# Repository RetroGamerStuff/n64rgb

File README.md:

# N64 RGB 

A collection of RGB mods for the N64. This repository includes:

- a simple RGB amp
  * based on TI's video amplifier THS7374 / THS7373 (only for some NTSC-units)
  * folder: simpleRGBAmp
- a general RGB digital-to-analog converter based on viletims schematics
  * supported devices: MaxII (EPM240T100C5, EPM570T100C5) and MaxV (5M240ZT100C4, 5M570ZT100C4) CPLDs
  * PCB files (common for all supported devices) and firmware (separate programming files) are provided
  * folder: generalRGBmod
- an advanced RGB digital-to-analog converter with optional YPbPr conversion
  * supported FPGA: Cyclone IV EP4CE10E22 and Cyclone 10 LP 10CL010YE144
  * PCB files (common for all supported devices) and firmware (separate programming files) are provided
  * additional Filter board for the outputted video signal if you need that
  * folder: advancedRGBmod
- additional RCP-NUS Adapter (flexible PCB):
  * buffering of video signals for N64RGB/N64Adv installs with wires
  * PCB files provided
  * folder: misc/RCP2Pads
- additional RCP-NUS to N64RGBv2.1/N64Adv install adapter (long flexible PCB):
  * buffering of video signals for N64RGBv2.1/N64Adv
  * can be directly connected to modding board
  * PCB files provided
  * folder: misc/RCP2N64RGB
- Filter AddOn for N64RGBv2 and N64 Advanced:
  * used to filter the video signal comming out of the ADV7125 or to adjust signal levels such that one can use SNES PAL RGB cables
  * PCB files provided
  * folder: misc/FilterAddOn
- Filter AddOn as flexible PCB for N64RGBv2.1 and N64 Advanced:
  * used to filter the video signal comming out of the ADV7125 or to adjust signal levels such that one can use SNES PAL RGB cables
  * PCB files provided
  * folder: misc/N64RGB2MoutFilter
- additional power supply PCB for viletime N64RGB DAC and N64RGBv1
  * PCB files provided
  * folder: misc/PowerReg

## Acknowledgement

Of course, many thanks to viletim for his initial CPLD-based DAC project, for providing a valuable commercial modding board as well as for publishing the schematics and source codes for that project.
I also want to send many thanks to Ikari_01. He has written the code to detect 480i and PAL/NTSC output with the CPLD. He provides a source code for the XC9572XL, which can be accessed here: [URL to Ikari_01's GitHub repository](https://github.com/mrehkopf/n64rgb)
Last but not least, thank you to Bob for his website [RetroRGB](http://retrorgb.com) and especially in this context here for collecting and sharing all the [RGB information regarding the N64](http://retrorgb.com/n64.html).

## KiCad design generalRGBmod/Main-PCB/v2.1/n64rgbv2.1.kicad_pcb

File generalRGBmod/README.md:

# General N64 RGB Digital-to-Analog Mod

This folder contains all you need for a complete DIY RGB mod.

Please don't ask me for selling a modding. I either sell some prototypes on some forums marketplaces (which is very unlikely) or I don't have any of the boards.
This is a complete DIY modding project. So everybody is on his own here.
If you are looking for a ready to install kit, just look on your own for a seller. Preferably you should invest your money into a [kit made by viletim](http://etim.net.au/shop/shop.php?crn=209). I also provide similar firmware files for his board in another GitHub repository named [n64rgb_fw4viletim](https://github.com/borti4938/n64rgb_fw4viletim) (note that I do not provide support for the firmware port there).

**WARNING:** This is an advanced DIY project if you do everything on your own. You need decent soldering skills. The CPLD has 0.5mm fine pitch with 100pins. Next to it the video amp has a 0.65mm pin pitch on the board there are some SMD1206 resistor and ferrit bead arrays.

## Features

- Supporting for different CPLDs on a common PCB design:
  * MaxII EPM240T100C5
  * MaxII EPM570T100C5
  * MaxV 5M240ZT100C5
  * MaxV 5M570ZT100C5
- Video DAC:
  * V2: Video DAC ADV7125
- Detection of 240p/288p vs. 480i/576i together with detection of NTSC vs. PAL mode
- optional VI-De-Blur in 240p/288p (horizontal resolution decreased from 640 to 320 pixels)
- optional 16bit color mode
- IGR features:
  * reset the console with the controller (can be disabled via jumper)
  * full control on de-blur and 16bit mode with the controller (can be disabled via jumper)
- optional dedicated mechanical switches for toggling VI-Deblur and 16bit color mode

The following shortly describes the main features of the firmware and how to use / control them.

#### Notes

### In-Game Routines (IGR)

Three functionalities are implemented: toggle de-blur feature and toggle the 16bit mode as well as resetting the console.

The button combination are as follows:

- reset the console: Z + Start + R + A + B
- (de)activate de-blur:
  - deactivate: Z + Start + R + C-le
  - activate: Z + Start + R + C-ri
- (de)activate 16bit mode:
  - deactivate: Z + Start + R + C-up
  - activate: Z + Start + R + C-dw

_Modifiying the IGR Button Combinations_:  
It's difficult to make everybody happy with it. Third party controllers, which differ from the original ones by design, make it even more difficult. So it is possible to generate your own firmware with **your own** preferred **button combinations** implemented. Please refere to the document **IGR.README.md** located in the top folder of this repository for further information.

_Final remark on IGR_:  
However, as the communication between N64 and the controller goes over a single wire, sniffing the input is not an easy task (and probably my solution is not the best one). This together with the lack of an exhaustive testing (many many games out there as well my limited time), I'm looking forward to any incomming issue report to furhter improve this feature :)

### VI-DeBlur

VI-Deblur of the picture information is only be done in 240p/288p. This is be done by simply blanking every second pixel. Normally, the blanked pixels are used to introduce blur by the N64 in 240p/288p mode. However, some games like Mario Tennis, 007 Goldeneye, and some others use these pixel for additional information rather than for blurring effects. In other words this means that these games uses full horizontal resolution even in 240p/288p output mode. Hence, the picture looks more blurry in this case if de-blur feature is activated.

### 16bit Color Mode

The 16bit color mode reduces the color depth from 21bit (7bit for each color) downto 16bits (5bit for red and blue, 6bit for green). Some very few games processes the color information in 16bit. The 16bit color mode simply sets LSBs to '0'.

### Jumpers

There are five jumpers on the modding board - two double solder jumper and three standard jumper.  
For double jumper, jumper Jxx.1 is indicated by an arrow, Jxx.2 is on the opposite side.

- J11.1 -> activates VI-deblur if closed. **[1]**
- J11.2 -> activates 16bit color mode **[1]**
- J12.x -> disables IGR functions if closed
  - x.1: VI-DeBlur and 16bit mode toggle by controller
  - x.2: reset by controller
- J21 -> enables Sync on Green if closed
- J31 -> 75ohm CSync Level
  - open: ~1.87Vpp at a 75ohm termination, i.e. you need an additional resistor in your RGB cables sync line to further attenuate voltage level
  - closed: ~300mVpp at a 75ohm termination, which is standard, i.e. you must not have any components attached to your RGB cables sync line
- J2: toggles video low pass filter of the Filter AddOn
  - open: enabled
  - closed: bypassed 

**Notes**:  

**[1]**  
Jumper becomes active on power cycle or if toggled while running operation.  

## Technical Information

A complete installation and setup guide to this modding kit is provided in the main folder of the repository. Here are some additional short notes.

### Checklist: How to build the project

- Use PCB files to order your own PCB or simply use the shared project on OSHPark
- Source the components you need, e.g. from Mouser
- Wait for everything to arrive
- Assemble your PCB:
  * If you use a MaxII CPLD, you have to assemble FB3 and must not use U4, C41 and C42.
  * If you use a MaxV CPLD, you need U4 (a 1.8V voltage regulator), C41 and C42. Don't touch FB3 in this case!
- Flash the firmware to the CPLD:
  * You need a Altera USB Blaster
  * The board needs to be powered; so you may consider to install the PCB into your N64 first and then use the N64 for powering the board
  * If you want to build an adapter, you may take a look onto [my DIY adapter](https://oshpark.com/shared_projects/mEwjoesz) at [my profile on OSHPark](https://oshpark.com/profiles/borti4938)
- Install the modding board:
  * Installation description is part of the guide located in the top folder.
  * However an installation guide of a similar product made by viletim is provided [here](http://etim.net.au/n64rgb/). Keep in mind that there are minor differences.
  * You have to be aware of the pinout of your video-encoder build into your N64. Pads on the DIY modding board are labeled.

### Source the PCB
Choose the PCB service which suits you. Here are some:

- OSHPark: look onto [my profile](https://oshpark.com/profiles/borti4938)
- PCBWay.com: [Link](http://www.pcbway.com/), [Affiliate Link](http://www.pcbway.com/setinvite.aspx?inviteid=10658)

### BOM / Part List for the PCB
This part list a recommendation how the PCB is designed. If you are able to find pin-compatible devices / parts, you can use them.

The manufacturer's part numbers (MPNs) are just to help you to source appropriate components.

### Firmware
The firmware is located in the folder firmware/. To build the firmware on your own you need Quartus Prime Lite (any version which supports MaxII and MaxV devices).

If you only want to flash the firmware, the configuration files are pre-compiled and located in firmware/output_files. You need the POF appropriate for the CPLD you have choosen (look for the *\_extension*).

For flashing you need:

- Altera USB Blaster
- Standalone Quartus Prime Programmer and Tools

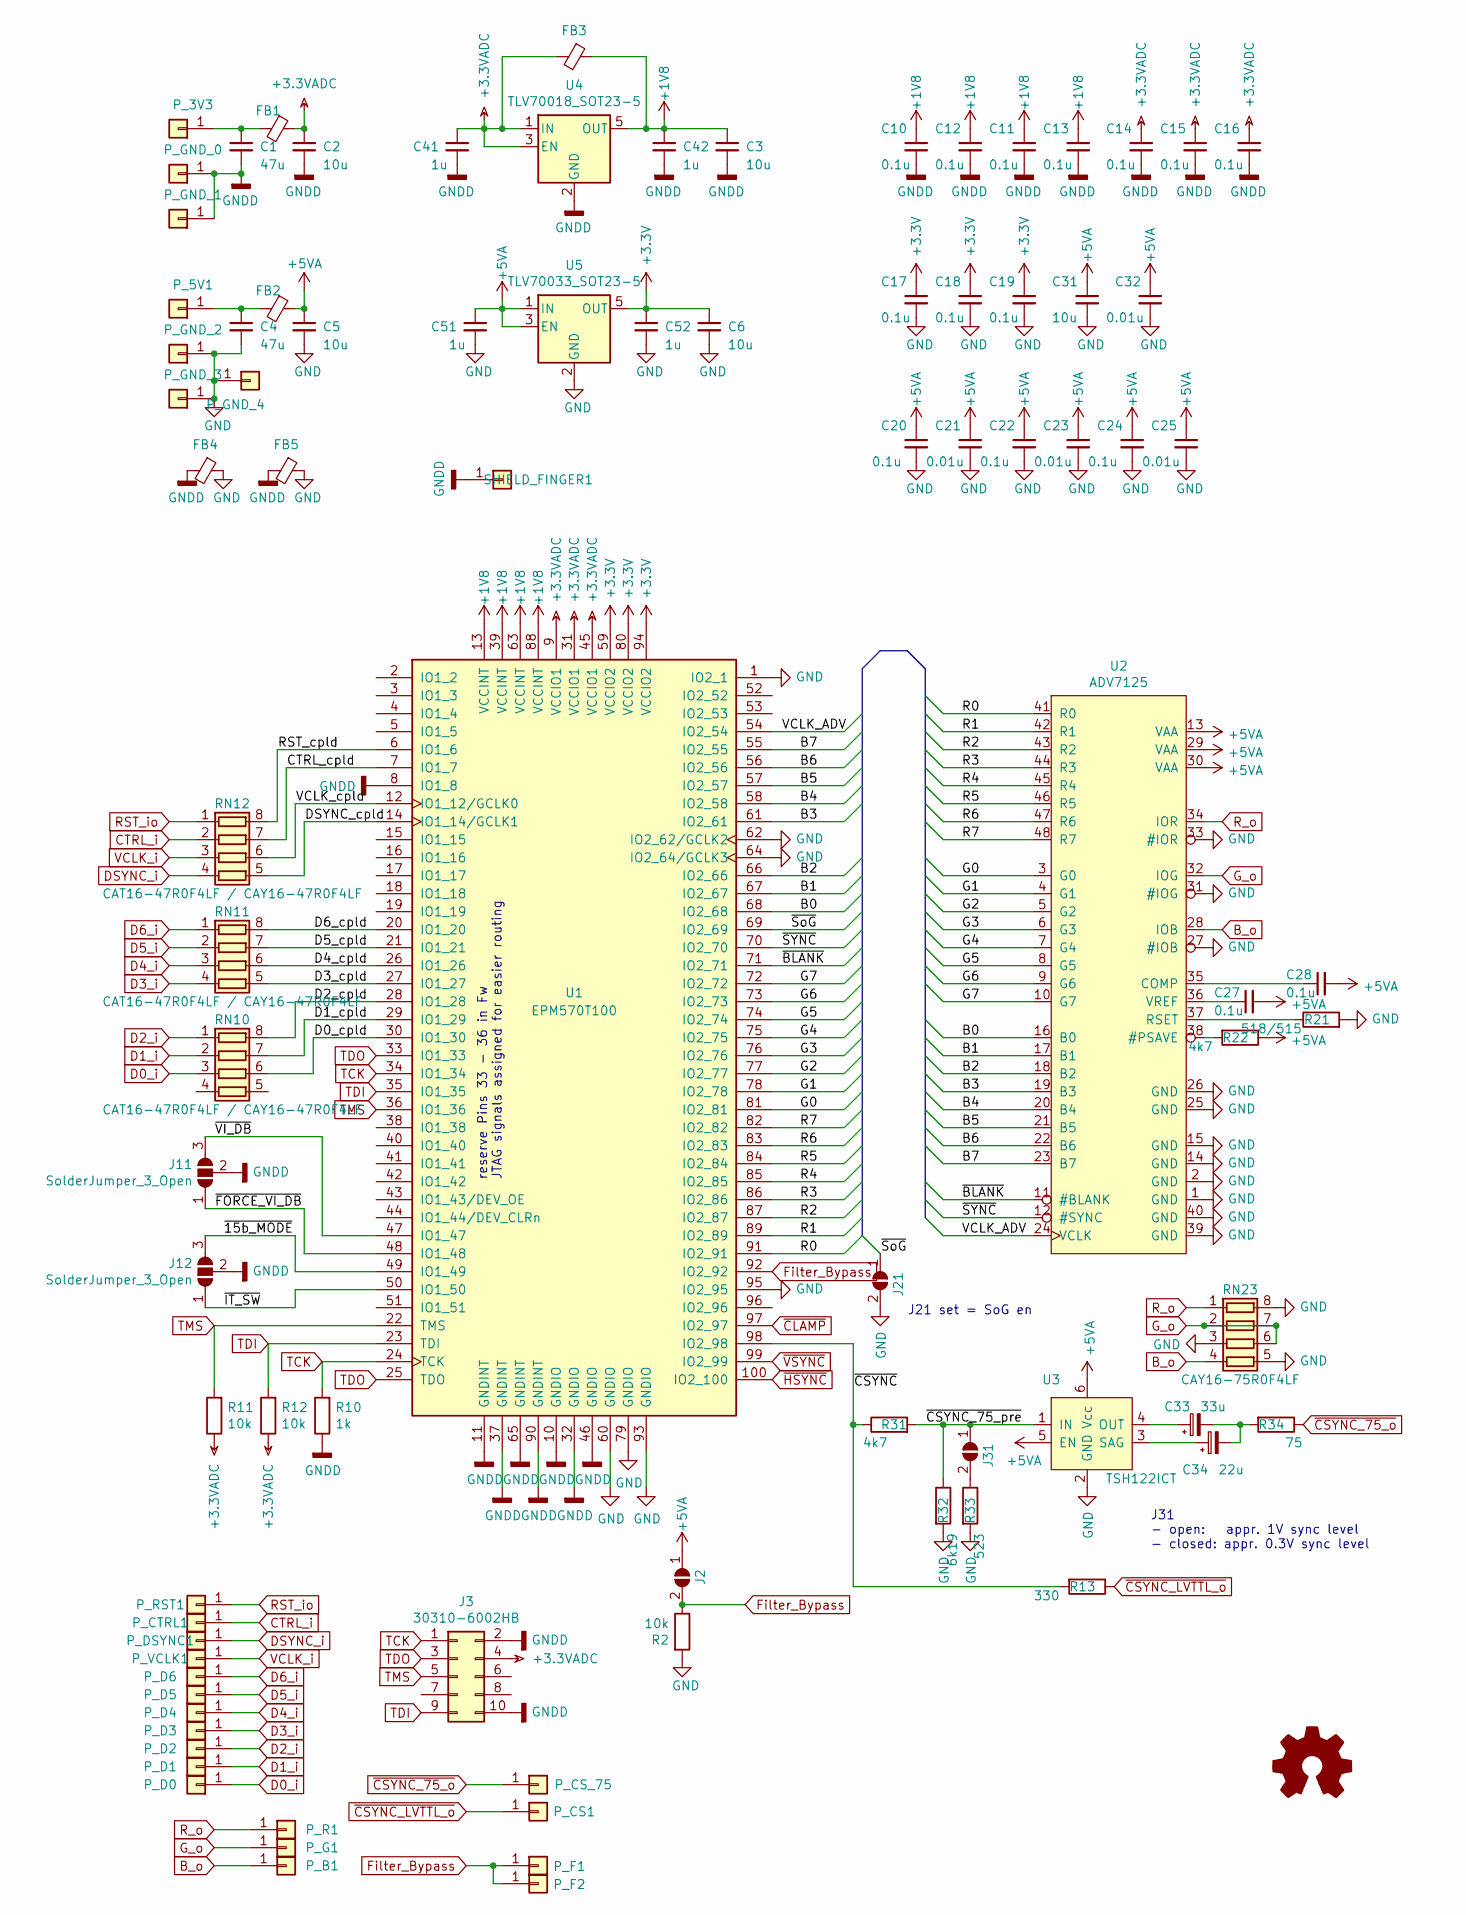
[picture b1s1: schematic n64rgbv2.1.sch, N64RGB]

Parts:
C1, C4: 47u; C_0805_2012Metric_Pad1.15x1.40mm_HandSolder
C2, C3, C5, C6, C31: 10u; C_0805_2012Metric_Pad1.15x1.40mm_HandSolder
C10, C11, C12, C13, C14, C15, C16, C17, C18, C19, C20, C22, C24, C27, C28: 0.1u; C_0603_1608Metric_Pad1.05x0.95mm_HandSolder
C21, C23, C25, C32: 0.01u; C_0603_1608Metric_Pad1.05x0.95mm_HandSolder
C33: 33u; C_0805_2012Metric_Pad1.15x1.40mm_HandSolder
C34: 22u; C_0805_2012Metric_Pad1.15x1.40mm_HandSolder
C41, C42, C51, C52: 1u; C_0603_1608Metric_Pad1.05x0.95mm_HandSolder
FB1, FB2, FB3, FB4, FB5: MPZ1608S221ATA00; R_0603_1608Metric_Pad1.05x0.95mm_HandSolder
J2, J21, J31: SolderJumper_2_Open; SolderJumper-2_P1.3mm_Open_RoundedPad1.0x1.5mm
J3: 30310-6002HB; PinHeader_2x05_P2.54mm_Vertical
J11, J12: SolderJumper_3_Open; SolderJumper-3_P1.3mm_Open_RoundedPad1.0x1.5mm
P_3V3, P_5V1: Conn_01x01; Wirepad_1.27_2.54
P_B1: Conn_01x01; Wirepad_1.27_2.54
P_CS1: Conn_01x01; Wirepad_1.27_2.54
P_CS_75: Conn_01x01; Wirepad_1.27_2.54
P_CTRL1: Conn_01x01; Wirepad_0.8_1.6
P_D0, P_D1, P_D2, P_D3, P_D4, P_D5, P_D6: Conn_01x01; Wirepad_0.8_1.6
P_DSYNC1: Conn_01x01; Wirepad_0.8_1.6
P_F1, P_F2: Conn_01x01; Wirepad_1.27_2.54
P_G1: Conn_01x01; Wirepad_1.27_2.54
P_GND_0, P_GND_1, P_GND_2, P_GND_3, P_GND_4: Conn_01x01; Wirepad_1.27_2.54
P_R1: Conn_01x01; Wirepad_1.27_2.54
P_RST1: Conn_01x01; Wirepad_0.8_1.6
P_VCLK1: Conn_01x01; Wirepad_0.8_1.6
R2, R11, R12: 10k; R_0603_1608Metric_Pad1.05x0.95mm_HandSolder
R10: 1k; R_0603_1608Metric_Pad1.05x0.95mm_HandSolder
R13: 330; R_0603_1608Metric_Pad1.05x0.95mm_HandSolder
R21: 518/515; R_0603_1608Metric_Pad1.05x0.95mm_HandSolder
R22, R31: 4k7; R_0603_1608Metric_Pad1.05x0.95mm_HandSolder
R32: 6k19; R_0603_1608Metric_Pad1.05x0.95mm_HandSolder
R33: 523; R_0603_1608Metric_Pad1.05x0.95mm_HandSolder
R34: 75; R_0603_1608Metric_Pad1.05x0.95mm_HandSolder
RN10, RN11, RN12: CAT16-47R0F4LF / CAY16-47R0F4LF; R_Array_Convex_4x0603
RN23: CAY16-75R0F4LF; R_Array_Convex_4x0603
SHIELD_FINGER1: S1761-42R; Pad_4.5_3.0
U1: EPM570T100; TQFP-100_14x14mm_P0.5mm
U2: ADV7125; LQFP-48_7x7mm_P0.5mm
U3: TSH122ICT; SC-70-6
U4: TLV70018_SOT23-5; SOT-23-5_HandSoldering
U5: TLV70033_SOT23-5; SOT-23-5_HandSoldering

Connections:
+1V8: C3.1, C10.1, C11.1, C12.1, C13.1, C42.1, FB3.1, U1.13 (VCCINT), U1.39 (VCCINT), U1.63 (VCCINT), U1.88 (VCCINT), U4.5 (OUT)
+3.3VADC: C2.1, C14.1, C15.1, C16.1, C41.1, FB1.1, FB3.2, J3.4, R11.1, R12.1, U1.9 (VCCIO1), U1.31 (VCCIO1), U1.45 (VCCIO1), U4.1 (IN), U4.3 (EN)
+3V3: C6.1, C17.1, C18.1, C19.1, C52.1, U1.59 (VCCIO2), U1.80 (VCCIO2), U1.94 (VCCIO2), U5.5 (OUT)
+5VA: C5.1, C20.1, C21.1, C22.1, C23.1, C24.1, C25.1, C27.2, C28.2, C31.1, C32.1, C51.1, FB2.1, J2.1 (A), R22.1, U2.13 (VAA), U2.29 (VAA), U2.30 (VAA), U3.5 (EN), U3.6 (Vcc), U5.1 (IN), U5.3 (EN)
/B0: U1.68 (IO2_68), U2.16 (B0)
/B1: U1.67 (IO2_67), U2.17 (B1)
/B2: U1.66 (IO2_66), U2.18 (B2)
/B3: U1.61 (IO2_61), U2.19 (B3)
/B4: U1.58 (IO2_58), U2.20 (B4)
/B5: U1.57 (IO2_57), U2.21 (B5)
/B6: U1.56 (IO2_56), U2.22 (B6)
/B7: U1.55 (IO2_55), U2.23 (B7)
/CTRL_cpld: RN12.7 (R2.2), U1.7 (IO1_7)
/D0_cpld: RN10.6 (R3.2), U1.30 (IO1_30)
/D1_cpld: RN10.7 (R2.2), U1.29 (IO1_29)
/D2_cpld: RN10.8 (R1.2), U1.28 (IO1_28)
/D3_cpld: RN11.5 (R4.2), U1.27 (IO1_27)
/D4_cpld: RN11.6 (R3.2), U1.26 (IO1_26)
/D5_cpld: RN11.7 (R2.2), U1.21 (IO1_21)
/D6_cpld: RN11.8 (R1.2), U1.20 (IO1_20)
/DSYNC_cpld: RN12.5 (R4.2), U1.14 (IO1_14/GCLK1)
/G0: U1.81 (IO2_81), U2.3 (G0)
/G1: U1.78 (IO2_78), U2.4 (G1)
/G2: U1.77 (IO2_77), U2.5 (G2)
/G3: U1.76 (IO2_76), U2.6 (G3)
/G4: U1.75 (IO2_75), U2.7 (G4)
/G5: U1.74 (IO2_74), U2.8 (G5)
/G6: U1.73 (IO2_73), U2.9 (G6)
/G7: U1.72 (IO2_72), U2.10 (G7)
/R0: U1.91 (IO2_91), U2.41 (R0)
/R1: U1.89 (IO2_89), U2.42 (R1)
/R2: U1.87 (IO2_87), U2.43 (R2)
/R3: U1.86 (IO2_86), U2.44 (R3)
/R4: U1.85 (IO2_85), U2.45 (R4)
/R5: U1.84 (IO2_84), U2.46 (R5)
/R6: U1.83 (IO2_83), U2.47 (R6)
/R7: U1.82 (IO2_82), U2.48 (R7)
/RST_cpld: RN12.8 (R1.2), U1.6 (IO1_6)
/VCLK_ADV: U1.54 (IO2_54), U2.24 (VCLK)
/VCLK_cpld: RN12.6 (R3.2), U1.12 (IO1_12/GCLK0)
/VIDeBlur_t: J11.1 (A), U1.48 (IO1_48)
/en_IGR_DeBl_15b_Func: J12.1 (A), U1.50 (IO1_50)
/en_IGR_Rst_Func: J12.3 (B), U1.49 (IO1_49)
/~15b_mode_t: J11.3 (B), U1.47 (IO1_47)
/~BLANK: U1.71 (IO2_71), U2.11 (#BLANK)
/~CSYNC: R13.2, R31.1, U1.98 (IO2_98)
/~CSYNC_75_pre: J31.1 (A), R31.2, R32.1, U3.1 (IN)
/~SYNC: U1.70 (IO2_70), U2.12 (#SYNC)
/~SoG: J21.1 (A), U1.69 (IO2_69)
B_o: P_B1.1, RN23.4 (R4.1), U2.28 (IOB)
CTRL_i: P_CTRL1.1, RN12.2 (R2.1)
D0_i: P_D0.1, RN10.3 (R3.1)
D1_i: P_D1.1, RN10.2 (R2.1)
D2_i: P_D2.1, RN10.1 (R1.1)
D3_i: P_D3.1, RN11.4 (R4.1)
D4_i: P_D4.1, RN11.3 (R3.1)
D5_i: P_D5.1, RN11.2 (R2.1)
D6_i: P_D6.1, RN11.1 (R1.1)
DSYNC_i: P_DSYNC1.1, RN12.4 (R4.1)
Filter_Bypass: J2.2 (B), P_F1.1, P_F2.1, R2.1, U1.92 (IO2_92)
GND: C4.2, C5.2, C6.2, C17.2, C18.2, C19.2, C20.2, C21.2, C22.2, C23.2, C24.2, C25.2, C31.2, C32.2, C51.2, C52.2, FB4.1, FB5.1, J21.2 (B), P_GND_2.1, P_GND_3.1, P_GND_4.1, R2.2, R21.2, R32.2, R33.2, RN23.3 (R3.1), RN23.5 (R4.2), RN23.8 (R1.2), U1.1 (IO2_1), U1.60 (GNDIO), U1.62 (IO2_62/GCLK2), U1.64 (IO2_64/GCLK3), U1.79 (GNDIO), U1.93 (GNDIO), U1.95 (IO2_95), U2.1 (GND), U2.2 (GND), U2.14 (GND), U2.15 (GND), U2.25 (GND), U2.26 (GND), U2.27 (#IOB), U2.31 (#IOG), U2.33 (#IOR), U2.39 (GND), U2.40 (GND), U3.2 (GND), U5.2 (GND)
GNDD: C1.2, C2.2, C3.2, C10.2, C11.2, C12.2, C13.2, C14.2, C15.2, C16.2, C41.2, C42.2, FB4.2, FB5.2, J3.2, J3.10, J11.2 (C), J12.2 (C), P_GND_0.1, P_GND_1.1, R10.1, SHIELD_FINGER1.1, U1.8 (IO1_8), U1.10 (GNDIO), U1.11 (GNDINT), U1.32 (GNDIO), U1.37 (GNDINT), U1.46 (GNDIO), U1.65 (GNDINT), U1.90 (GNDINT), U4.2 (GND)
G_o: P_G1.1, RN23.2 (R2.1), RN23.6 (R3.2), RN23.7 (R2.2), U2.32 (IOG)
unnamed: C1.1, FB1.2, P_3V3.1
unnamed: C4.1, FB2.2, P_5V1.1
unnamed: C27.1, U2.36 (VREF)
unnamed: C28.1, U2.35 (COMP)
unnamed: C33.1, U3.4 (OUT)
unnamed: C33.2, C34.2, R34.2
unnamed: C34.1, U3.3 (SAG)
unnamed: J31.2 (B), R33.1
unnamed: R21.1, U2.37 (RSET)
unnamed: R22.2, U2.38 (#PSAVE)
RST_io: P_RST1.1, RN12.1 (R1.1)
R_o: P_R1.1, RN23.1 (R1.1), U2.34 (IOR)
TCK: J3.1, R10.2, U1.24 (TCK), U1.34 (IO1_34)
TDI: J3.9, R12.2, U1.23 (TDI), U1.35 (IO1_35)
TDO: J3.3, U1.25 (TDO), U1.33 (IO1_33)
TMS: J3.5, R11.2, U1.22 (TMS), U1.36 (IO1_36)
VCLK_i: P_VCLK1.1, RN12.3 (R3.1)
~CLAMP: U1.97 (IO2_97)
~CSYNC_75_o: P_CS_75.1, R34.1
~CSYNC_LVTTL_o: P_CS1.1, R13.1
~HSYNC: U1.100 (IO2_100)
~VSYNC: U1.99 (IO2_99)

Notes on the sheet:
J21 set = SoG en
J31 - open: appr. 1V sync level - closed: appr. 0.3V sync level
reserve Pins 33 - 36 in Fw JTAG signals assigned for easier routing

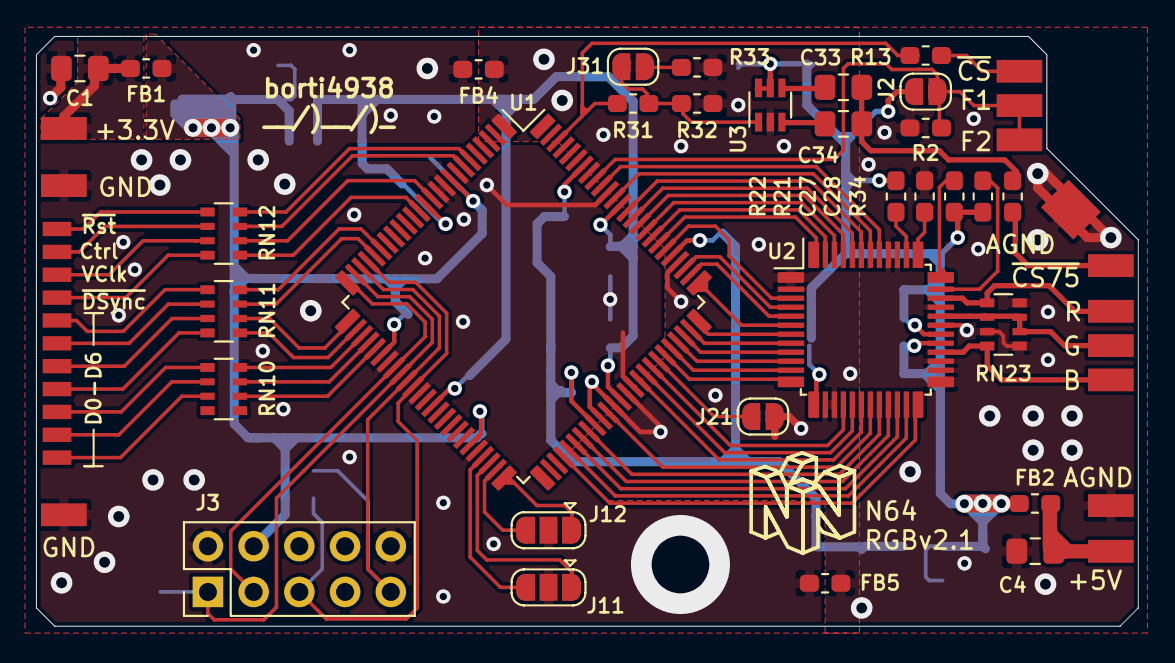
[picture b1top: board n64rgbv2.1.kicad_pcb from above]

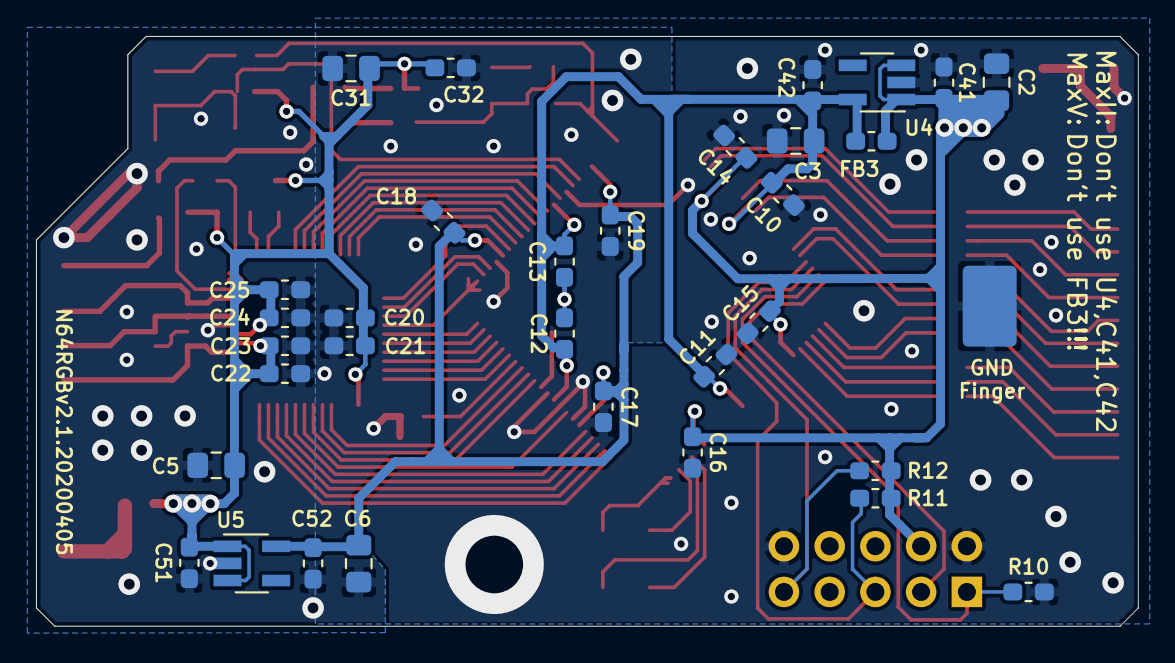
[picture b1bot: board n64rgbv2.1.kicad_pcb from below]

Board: 2 copper layers, 61.2 x 32.8 mm, 89 parts (33 on the bottom side), 82 nets.

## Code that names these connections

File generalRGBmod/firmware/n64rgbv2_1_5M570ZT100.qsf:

# -------------------------------------------------------------------------- #
#
# Copyright (C) 1991-2016 Altera Corporation. All rights reserved.
# Your use of Altera Corporation's design tools, logic functions
# and other software and tools, and its AMPP partner logic
# functions, and any output files from any of the foregoing
# (including device programming or simulation files), and any
# associated documentation or information are expressly subject
# to the terms and conditions of the Altera Program License
# Subscription Agreement, the Altera Quartus Prime License Agreement,
# the Altera MegaCore Function License Agreement, or other
# applicable license agreement, including, without limitation,
# that your use is for the sole purpose of programming logic
# devices manufactured by Altera and sold by Altera or its
# authorized distributors.  Please refer to the applicable
# agreement for further details.
#
# -------------------------------------------------------------------------- #
#
# Quartus Prime
# Version 15.1.2 Build 193 02/01/2016 SJ Lite Edition
# Date created = 08:12:51  July 18, 2016
#
# -------------------------------------------------------------------------- #
#
# Notes:
#
# 1) The default values for assignments are stored in the file:
#		n64rgb_with_igr_assignment_defaults.qdf
#    If this file doesn't exist, see file:
#		assignment_defaults.qdf
#
# 2) Altera recommends that you do not modify this file. This
#    file is updated automatically by the Quartus Prime software
#    and any changes you make may be lost or overwritten.
#
# -------------------------------------------------------------------------- #


set_global_assignment -name FAMILY "MAX V"
set_global_assignment -name DEVICE 5M570ZT100C5
set_global_assignment -name ORIGINAL_QUARTUS_VERSION 18.1.0
set_global_assignment -name PROJECT_CREATION_TIME_DATE "14:45:41  MARCH 05, 2019"
set_global_assignment -name LAST_QUARTUS_VERSION "20.1.1 Lite Edition"
set_global_assignment -name MIN_CORE_JUNCTION_TEMP 0
set_global_assignment -name MAX_CORE_JUNCTION_TEMP 85
set_global_assignment -name DEVICE_FILTER_PACKAGE TQFP
set_global_assignment -name DEVICE_FILTER_PIN_COUNT 100
set_global_assignment -name ERROR_CHECK_FREQUENCY_DIVISOR "-1"
set_global_assignment -name STRATIX_DEVICE_IO_STANDARD "3.3-V LVTTL"


## N64 Video Input
## ===============
set_location_assignment PIN_12 -to VCLK
set_location_assignment PIN_14 -to nDSYNC
set_location_assignment PIN_30 -to D_i[0]
set_location_assignment PIN_29 -to D_i[1]
set_location_assignment PIN_28 -to D_i[2]
set_location_assignment PIN_27 -to D_i[3]
set_location_assignment PIN_26 -to D_i[4]
set_location_assignment PIN_21 -to D_i[5]
set_location_assignment PIN_20 -to D_i[6]

set_instance_assignment -name GLOBAL_SIGNAL GLOBAL_CLOCK -to VCLK
set_instance_assignment -name GLOBAL_SIGNAL GLOBAL_CLOCK -to nDSYNC


## Controller and Reset
## ====================
set_location_assignment PIN_6 -to nRST_io
set_location_assignment PIN_7 -to CTRL_i

set_instance_assignment -name WEAK_PULL_UP_RESISTOR ON -to nRST_io
set_instance_assignment -name WEAK_PULL_UP_RESISTOR ON -to CTRL_i


## Video Output to ADV7125
## =======================
set_location_assignment PIN_91 -to R_o[0]
set_location_assignment PIN_89 -to R_o[1]
set_location_assignment PIN_87 -to R_o[2]
set_location_assignment PIN_86 -to R_o[3]
set_location_assignment PIN_85 -to R_o[4]
set_location_assignment PIN_84 -to R_o[5]
set_location_assignment PIN_83 -to R_o[6]
set_location_assignment PIN_82 -to R_o[7]
set_location_assignment PIN_81 -to G_o[0]
set_location_assignment PIN_78 -to G_o[1]
set_location_assignment PIN_77 -to G_o[2]
set_location_assignment PIN_76 -to G_o[3]
set_location_assignment PIN_75 -to G_o[4]
set_location_assignment PIN_74 -to G_o[5]
set_location_assignment PIN_73 -to G_o[6]
set_location_assignment PIN_72 -to G_o[7]
set_location_assignment PIN_68 -to B_o[0]
set_location_assignment PIN_67 -to B_o[1]
set_location_assignment PIN_66 -to B_o[2]
set_location_assignment PIN_61 -to B_o[3]
set_location_assignment PIN_58 -to B_o[4]
set_location_assignment PIN_57 -to B_o[5]
set_location_assignment PIN_56 -to B_o[6]
set_location_assignment PIN_55 -to B_o[7]

set_location_assignment PIN_97 -to nCLAMP
set_location_assignment PIN_98 -to nCSYNC
set_location_assignment PIN_99 -to nVSYNC
set_location_assignment PIN_100 -to nHSYNC

set_location_assignment PIN_54 -to CLK_ADV712x
set_location_assignment PIN_70 -to nCSYNC_ADV712x
set_location_assignment PIN_71 -to nBLANK_ADV712x

set_instance_assignment -name SLOW_SLEW_RATE ON -to nCSYNC
set_instance_assignment -name SLOW_SLEW_RATE ON -to nHSYNC
set_instance_assignment -name SLOW_SLEW_RATE ON -to nCLAMP
set_instance_assignment -name SLOW_SLEW_RATE ON -to nVSYNC


## Jumper
## ======
set_location_assignment PIN_69 -to nSYNC_ON_GREEN
set_location_assignment PIN_47 -to n16bit_mode_t
set_location_assignment PIN_48 -to nVIDeBlur_t
set_location_assignment PIN_49 -to en_IGR_Rst_Func
set_location_assignment PIN_50 -to en_IGR_DeBl_16b_Func

set_instance_assignment -name WEAK_PULL_UP_RESISTOR ON -to nSYNC_ON_GREEN
set_instance_assignment -name WEAK_PULL_UP_RESISTOR ON -to n16bit_mode_t
set_instance_assignment -name WEAK_PULL_UP_RESISTOR ON -to nVIDeBlur_t
set_instance_assignment -name WEAK_PULL_UP_RESISTOR ON -to en_IGR_Rst_Func
set_instance_assignment -name WEAK_PULL_UP_RESISTOR ON -to en_IGR_DeBl_16b_Func


## Others
## ======
set_location_assignment PIN_33 -to dummy_i[4]
set_location_assignment PIN_34 -to dummy_i[3]
set_location_assignment PIN_35 -to dummy_i[2]
set_location_assignment PIN_36 -to dummy_i[1]
set_location_assignment PIN_92 -to dummy_i[0]



## Files
## =====
set_global_assignment -name TOP_LEVEL_ENTITY n64rgbv2_top

set_global_assignment -name VERILOG_INCLUDE_FILE vh/n64rgb_params.vh
set_global_assignment -name VERILOG_INCLUDE_FILE vh/igr_params.vh

set_global_assignment -name VERILOG_FILE rtl/n64rgbv2_top.v
set_global_assignment -name VERILOG_FILE rtl/n64rgb_hk.v
set_global_assignment -name VERILOG_FILE rtl/n64_vdemux.v
set_global_assignment -name VERILOG_FILE rtl/n64_vinfo_ext.v

set_global_assignment -name SDC_FILE sdc/n64rgbv2.sdc

set_global_assignment -name PROJECT_OUTPUT_DIRECTORY output_files/5M570ZT100


## Synthesis and Fitter Settings
## =============================
set_global_assignment -name SMART_RECOMPILE ON
set_global_assignment -name RESERVE_ALL_UNUSED_PINS "AS INPUT TRI-STATED WITH BUS-HOLD"
set_global_assignment -name OPTIMIZATION_MODE "HIGH PERFORMANCE EFFORT"


## Additions by Quartus Prime
## ==========================
set_global_assignment -name POWER_PRESET_COOLING_SOLUTION "NO HEAT SINK WITH STILL AIR"
set_global_assignment -name ENABLE_OCT_DONE OFF
set_global_assignment -name STRATIXV_CONFIGURATION_SCHEME "PASSIVE SERIAL"
set_global_assignment -name USE_CONFIGURATION_DEVICE ON

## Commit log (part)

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2018-02-08 yet another bugfix (incl. builds)
2018-02-08 a lot of refactoring stuff: - register some logic - remove some redundant registers - improve 480i/576i detection - commit includes fw-builds
2018-02-09 reviewing some deblur stuff (stability of estimation, especially on CPLD versions)
2018-02-09 VI-Deblur bugfix
2018-02-09 some more VI-Deblur and register replacement stuff
2018-02-16 update configuration structure: - organized in 4x 8bit words - some bits reserved for future use
2018-02-16 use flash functions only if first check haven't failed
2018-02-17 minor bugfixes
2018-02-17 small bugfix (trend were decreased while estimation was not running)
2018-02-18 osd params corrected
2018-02-18 misc updates: - increase compared number of bits for deblur estimation - small bug fix (trend was decreased if estimation were not running) - minimize area during synthesis to get a closer match to f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
2018-02-18 provide (hopefully) stable programming files
2018-02-18 programming files for latest changes
2018-02-19 do not execute load/save from/to flash if not initialized
2018-02-19 remove obsolete leavetype
2018-02-19 add some comments
2018-02-20 some small bugfixes
2018-02-21 - Test-Update: latch input data on rising edge instead of falling edge - optimize hold timing on all paths (which seems to have no effect on the CPLD versions) - remove two falsely set synthesis and 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
2018-02-22 add timing constraints and remove synthesis assignment to met timing analysis
2018-02-22 re-introduce half pixel shift removing between deblur on and off
2018-02-22 move osd menu to the rigth for PAL mode
2018-02-22 small text adaptation
2018-03-08 add smart recompile to qsf
2018-03-08 add setup and hold time from ADV7125 to timing constraints
2018-03-08 add programming files and update project files
2018-03-09 new programming files, update project files and small quick bugfix in advanced project
2018-03-17 option for hybrid scanlines
2018-03-17 small text update
2018-03-18 add "don't use scanlines in OSD menu" as an option
2018-03-25 logo implementation
2018-03-25 small font adaptation
2018-03-26 rename function apply_command to modify_menu
2018-03-27 firmware builds for recent commits
2018-04-05 Confirm load/save and minor improvements
2018-04-15 discontinue 6k LE FPGA support for now
2018-04-22 add menu to guide
2018-05-01 third party controller support (e.g. Hori pad)
2018-05-09 bump to Quartus Prime 18.0
2018-05-10 Update BOM - fix some broken links (Mouser) of ICs - Replace U5 - Passive components untouched
2018-05-11 replace vdemux
2018-05-11 support ram pages
2018-05-11 bump also n64rgb to QP 18.0
2018-05-11 update programming and project files (incl. header in n64a top module) after recent commits
2018-05-26 info and warning window template
2018-05-26 add some pics
2018-05-27 remove unnecessarily committed file
2018-05-31 initial commit (RCP-NUS break out; untested)
2018-06-17 initial commit (RCP-NUS break out)
2018-06-22 Revert "refine linebuf.v to not rely on synthesis optimization"
    This reverts commit 3f9c6e86b52bf000c7d36ee04d0fb0e85d229fc9.
    Implementation was buggy - I'm sorry for any inconvenience caused
2018-07-20 remove vclk-pll for stability consernings in certain circumstances
2018-07-25 update PCB - add fields for GND shield fingers and remove pad for /COLD
2018-07-25 remove designs which are in experimental stage
2018-07-26 synchronize reset for video related blocks
2018-07-26 update programming files and fw-number
2018-08-14 add missing false path
2018-08-15 implementation of advanced scanline drawing technique This technique takes the previous line (even scanline) or the next (odd scanline) into account for calculation and drawing the scanline. This smo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
2018-08-16 parameterize number of buffer pages
2018-08-16 increase buffer size to five lines (by the costs of memory space for NIOS II soft core)
2018-08-16 stabilize 480i-linex2 output (reduce/no vertical twitching)
2018-08-16 scanlines in 480i linex2 mode allowed (no advanced scanlines)
2018-08-17 remove outdated comment
2018-08-17 update firmware number (equalization of subversion number of hard- and software code)
2018-08-20 increase buffer size (just because it fits)
2018-08-21 remove revision numbering in headers
2018-08-21 move gamma correction into a dedicated module (incl. update remaining header)
2018-08-21 increase false_path list
2018-08-21 update programming and project files for recent bug fixes
2018-08-22 correct reset values in rgb2ypbpr converter
2018-09-04 remove needless lines
2018-09-04 parameterize testpattern (alpha)
2018-09-13 file adaptations for new folder structure
2018-09-14 update project files for recent commits
2018-09-14 FPC adapter
2018-09-14 remove outdated file
2018-09-14 init commit of N64Adv2 firmware (not functional yet)
2018-09-14 update gitignore
2018-09-29 modify outline layer a bit
2018-09-29 bump to quartus prime 18.1
2018-10-11 bump to QP v18.1
2018-10-11 minor cosmetic changes
2018-10-11 add mising files and changes
2018-10-19 enable clock div mux output
2018-10-19 prepare separate scaler / linedoubler unit for N64Aadv1 and N64Adv2
2018-10-19 480p as default
2018-10-22 update on APU module: audio is now working
2018-10-30 remove header from constraint files
2018-10-30 alternating constraint on output paths hopefully removing color quirk
2018-11-04 correct and remove some remainings
2018-11-04 move DE gen into ADV and outline 240p support
2018-11-04 remove useless ports
2018-11-05 move sync generation to reading process, remove a useless port and tiny bugfix (glitchy linex2 in 480i due to tight timing)
2018-11-05 update project and firmware files
2018-11-06 remove useless value from OSDInfo vector
2018-11-06 add testbenches for APU
2018-11-11 remove connections for DE and MCLK and change pinout for system LEDs
2018-12-07 increase via at center of exposed pad for easier DIY soldering
2018-12-25 sync in reset for audio logic
2019-01-25 pcb update: add some additional pads for rst and ctrl io
2019-02-12 remove system clock enable from pinout (rely on weak pull-up)
2019-02-12 linex3 for 240p60 input and some cosmetic changes
2019-03-06 refactoring of timing analysis to improve fitting
2019-03-06 introduce new CPLD for N64RGBv1 and v2 which now meets timings
2019-03-17 refactoring reset logic and sync between asynchronous paths
2019-03-18 formatting stuff
2019-04-11 upload new design for RCP2Pads
2019-10-05 menu und functionality updates: - LineX2 without VPLL - optional VPLL use for LineX3 - Feedback channel from PPU to NIOS II (uC was guessing before)
2019-10-11 bugfix in BOM (thanks to Sefirosu789 and unmaker from shmups forumfor pointing that out!)
2019-10-14 yet another tinz bugfix plus fw. version update
2019-10-15 detecting FilterAddon properly and removing false friends in constant namings
2019-11-27 raw binary for production runs and easier DIY (for those who do not have a USB Blaster)
2020-01-20 update year in copyright notes
2020-01-20 control menu with analog stick
2020-01-20 simplify clock network
2020-01-20 minor update (weak pull up instead of bus hold for unused pins)
2020-01-22 bugfix in configureable deblur algorithm update fw files
2020-01-26 bank separation between digital video in and digital video outs using 2.5V LDO
2020-02-14 fix header quirk in mfiles
2020-02-14 update firmware files
2020-02-18 update firmware
2020-03-18 bugfix: misc menu wasn't working correctly for non-filter addon installs
2020-03-19 update firware files
2020-03-22 update N64Adv board: - csync level selection by jumper - output IO bank powered by 5V rail (over a 3.3V ldo)
2020-03-22 somne new production data for the filter addon board
2020-03-22 coordinate files
2020-03-22 N64RGBv2.1 - inputs and outputs separated at different IO Banks - outputs powered by 5V rail (over a 3.3V LDO) - PCB design allows for usage of flex designs (initially meant for the N64Adv) - PCB mad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
2020-04-05 incremental improvements after first prototype run
2020-07-05 remove firmware for viletims N64RGB from repository
2020-07-05 change duty cycle at pll out to 60% (same as input)
2020-07-08 alter timings a bit incl. adding a safety margin for tsu and th for ADV7125
2020-07-08 ignore controller inputs after opening the menu for a few frames
2020-07-08 update firmware and project files
2020-07-08 update BOM for new flex cable concept
2020-07-09 update and add some documentation
2020-07-12 bugfix: repair url to correct IC @ U7
2020-07-13 remove unneccessary registers
2020-07-13 new firmware files and new naming to make clear that firmware is for v2.1
2020-07-15 formatting
2020-07-15 remove magic numbers
2020-07-15 update fw no., project files and firmware files
2020-08-18 bug fixes and incremental improvements in gamma2rom.m script
2020-08-18 passing video data sync through all modules
2020-08-18 multicycle analysis - somehow tedious - might be simpler using something like 'set enabled_regs [get_fanouts [get_pins enable_reg|q] –through [get_pins –hierarchical *|ena]]'
2020-08-19 typo fix
2020-08-19 rework with sdc
2020-09-17 remove auto deblur stuff from N64RGB - I found more and more situations where the auto detection does not work reliable - so I removed it for now
2020-09-18 add THS7374 rgb amp by TzorriMahm as submodulee
2020-09-18 misc updates: - remove deblur heuristic function (same reason as for the N64RGBv2.1) - undo commits 7cbfe9ac1eb809ba2aa9ed5b957db946c618042d, ba99bacb24be1f8a60ceded04c9939a554467d6a, 1f774a66b1c449c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
2020-09-19 update input timings
2020-09-19 do not run JTAG through other pins as this may cause problem if used CPLDs are assembled
2020-09-19 update fw for older PCB versions (removing deblur heuristics)
    (cherry picked from commit 10f550d924fbe1fe2ecd3e1af62ef39604ccbc32)
2020-09-19 update BOM
    (cherry picked from commit c3bb21dca278fcc9a3faaef770ff45191a9fccf5)
2020-09-21 Update jumper and menu description
2020-11-28 fix unnecessary sign error in sdc
2020-11-28 bump to Quartus Prime Lite 20.1
2020-11-29 change vi-config pages a bit
2020-12-06 tiny fix: put not variable declaration in while(1) loop
2020-12-06 revise some numbers
2020-12-08 use valid data flag in order to account for 4x pixelclock
2020-12-12 register shift correction at output
2020-12-12 put wire and reg defs to top of file
2020-12-20 move gamma table offset definition from vparams to ppuconfig
2020-12-20 move OSD a bit to middle of the screen especially for PAL content (menu was at very left of the screen)
2020-12-27 tiny text adaptation
2020-12-27 tiny fix at preset value width
2020-12-31 16bit mode instead of 15bit (one bit more for green)
2021-01-04 name adaptations
2021-01-04 minor bug fix (nVDSYNC not part of sensitivity list)
2021-01-04 add default state to state machine
2021-01-04 remove outdated files
2021-01-05 tiny adaptations: - remove outdated lines - text fixes
2021-01-05 PPU update: - horizontal shift for passthrough mode (still needs work) - place testpattern infront of gamma module in order to use linex modes afterwards
2021-01-06 update firmware version
2021-01-06 update documentation (still an annoying task)
2021-01-07 firmware files for older v1 and v2 PCBs
    (cherry picked from commit f7c00406ce4fe6c302de748c701290437dd5368d)
2021-01-07 add changelog file for N64Adv firmware
2021-01-15 tiny tiny fixes
2021-01-15 buggfix: HV Sync was not working
2021-01-23 bug fix (impulse width counter was not resetted correctly, which reduced tolerance by half)
2021-01-26 move sysconfig to config.c/.h
2021-02-01 remove register, which is not used
2021-02-01 review implementation of osd_injection module
    (cherry picked from commit 01b561090bf988785a58571093a572e002666fe1)
2021-02-01 remove "begin ... end" (as not needed)
    (cherry picked from commit 36cb327da6bd7ef0298311bb64a74395c50c0816)
2021-02-02 fix some formatting issues
2021-02-07 update flash init and remove old commented lines
2021-03-26 update changelog
2021-03-26 show PPU feedback value in menu (might be useful for better support)
2021-03-26 fix nVSYNC detection for 4MHz clock
2021-03-26 fix video valid window
2021-03-26 tiny sdc fix
2021-04-08 some more documentation tweaks
